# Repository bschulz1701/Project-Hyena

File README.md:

# Project-Hyena
Daughterboard for use with Feather form factor controller, designed to interface with multiple, flexible, low cost sensors at the core of a low cost meteorological sensing system. 

# Repo Outline
#### [Documents](Documents/) 

General document and image storage for repo and README

#### [Hardware](Hardware/)

Current board files (Eagle), Bill of Materials (BoM), and other design documents

#### [Production](Production/)

Contains the various Gerber and pick and place files required to have the Printed Circuit Boards (PCBs) manufactured or populated 

#### [Software](Software/)

The software associated with the piece of hardware, this is usually diagnostic software used for verifying or investigating the hardware

#### [Testing](Testing/)

Scripts and results from the testing process and development process. Contains more detailed information about documented issues among other testing. 

## Overview
* **Type:** Data Logger/Daughterboard 
* **Interfaces:** I<sup>2</sup>C, GPIO, Pulse
* **Release Version:** v0.2 - 2020/07/15

## Features
### On-Board
* Micro SD Card 
* RTC w/Battery Backup
* Temperature/Pressure/RH Sensor
* RGB Ambient Light Sensor
* Reverse Polarity Power Protected Inputs 

### Interface
* Tipping Bucket Input (SPST switch compatible)
* Dedicated Potentiometric Input (x1) 
* Flexible Sensor Inputs (x3)
* Dedicated I<sup>2</sup>C Input (x1) 
* Supports Particle and other Feather based controllers 

## Specifications
* **Sensor Voltage:** 3.3V
* **Sensor Current (Max):** 500mA (Combined)

## Jumper Settings 

**Port Select Jumpers**
| Jumper | Purpose | Position 1 | Position 2 | 
| ------ | ------- | ---------- | ---------- |
| `JP1`	| GPIO vs I<sup>2</sup>C - Port 1 Digital | Select I2C | Select GPIO | 
| `JP2` | GPIO vs I<sup>2</sup>C - Port 1 Analog | Select I2C | Select GPIO | 
| `JP3` | GPIO vs I<sup>2</sup>C - Port 2 Digital | Select I2C | Select GPIO | 
| `JP4` | GPIO vs I<sup>2</sup>C - Port 2 Analog | Select I2C | Select GPIO | 
| `JP5` | GPIO vs I<sup>2</sup>C - Port 3 Digital | Select I2C | Select GPIO | 
| `JP6` | GPIO vs I<sup>2</sup>C - Port 3 Analog | Select I2C | Select GPIO | 
| `JP8` | Power Select (Core vs Ext) - Port 1 | Core Power for Port 1 | External Switched Power for Port 1 |

**Configuration Jumpers**
| Jumper | Purpose | Open | Closed | Default | 
| ------ | ------- | ---------- | ---------- | ----- | 
| `JP7` | Enable Hardware WDT | WDT Disabled | WDT Enabled | Closed |  
| `JP9` | Pullup for Port 1 Digital GPIO | Pullup Disabled | Pullup Enabled | Open |
| `JP10` | Gang On-Board and External I2C Buses | I2C Combined | I2C Isolated | Open | 

## Known Issues/Errata

#### WDT Disable

**Issue:** If using Particle Boron as controller and if you have the WDT disabled (leave `JP7` open), the system fails to run properly, or has sporadic resets. This is likely due to parasitic current on the reset line of the Boron.

**Workaround:** Make sure WDT is enabled by closing `JP7`

#### Solder Jumper Stencil

**Issue:** Depending on the thickness of the solder stencil used for populating the board, the solder jumpers may not bridge when desired. This is due to lack of stencil thickness specification and pad geometry.

**Workaround:** Make a note on the board assembly (if working with a board house) as to which jumpers should be connected (see jumper tables). Otherwise, if assembling manually, check the jumpers are connected, and bridge them using solder wire and a soldering iron if they have failed to jump where desired.

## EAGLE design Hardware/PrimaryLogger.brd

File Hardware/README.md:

# Hardware Overview - Project Hyena

## Files

* [Legacy](Legacy/) - File storage for older hardware versions  
* PrimaryLogger.sch - Eagle Schematic
* PrimaryLogger.brd - Eagle Board File
* [PrimaryLogger_BoM.csv](PrimaryLogger_BoM.csv) - BoM (For reference only, see [Production](../Production) for production ready BoM)
* [PrimaryLogger.pdf](PrimaryLogger_0v2.pdf) - PDF of Schematic 

## I2C Addresses 

| Device | Address | 
| ------ | ------- | 
| MCP23008 | 0x20 | 
| TCS3400 | 0x39 |
| MCP7940 | 0x6F |
| SHTC3 | 0x70 |

## Pinout

| Particle Pin | Hyena Pin Name | Control | Function | 
| ------------ | -------------- | ------- | -------- |
| 8 | `3V3_EXT_EN` | Output | Enables the external 3.3v rail (active high, nominally low) | 
| 7 | `WD_HOLD` | Output | Controls the hardware watchdog timer, pulse high to "feed" timer |
| 6 | `GPIO1D` | IO | General digital IO pin for external sensors (J1 Connector) | 
| 5 | `GPIO2D` | IO | General digital IO pin for external sensors (J2 Connector) | 
| 4 | `GPIO3D` | IO | General digital IO pin for external sensors (J3 Connector) | 
| 3 | `RTC_INT` | Input | Interrupt line from RTC, natively high active low (open drain), triggers on falling edge |
| 2 | `SDA_CTRL` | Output | Used to turn internal I2C on or off (active high, I2C_OB on, natively low) |
| 1 | `SCL` | Output | I2C clock line |
| 0 | `SDA` | IO | I2C Data line |
| 9 | `3V3_SD_EN` | Output | Enable line for SD card 3.3v supply (active high, natively low) |
| 10 | `IO_EXP_INT` | Input | Global interrupt from the IO expander (functionality configurable via software) |
| 11 | `MISO` | Input | MasterInSlaveOut, part of SPI bus |
| 12 | `MOSI` | Output | MasterOutSlaveIn, part of SPI bus | 
| 13 | `SCK` | Output | SerialClocK, part of SPI bus | 
| 14 | `SD_CS` | Output | SD chip select line, active low |
| 15/ADC4 | `TIP` | IO | Designed as tipping bucket rain gauge input, connected to J6, pulled high by default |
| 16/ADC3 | `GPIOXA` | IO | Intended as analog input for potentiometric input (J5) |
| 17/ADC2 | `GPIO1A` | IO | General digital/analog IO pin for external sensors (J1 Connector) |
| 18/ADC1 | `GPIO2A` | IO | General digital/analog IO pin for external sensors (J2 Connector) |
| 19/ADC0 | `GPIO3A` | IO | General digital/analog IO pin for external sensors (J3 Connector) |

| IO Expander Pin | Hyena Pin Name | Control | Function |
| --------------- | -------------- | ------- | -------- |
| 0 | `3V3_EXT_FAULT` | Input | Monitor pin for external 3v3 rail, if over current trip, pin is pulled low, natively high |
| 1 | `3V3_SD_FAULT` | Input | Monitor pin for SD card 3v3 rail, if over current trip, pin is pulled low, natively high |
| 2 | `SD_CD` | Input | Card detect pin for SD card, natively high, pulled low to indicate physical presence of SD card | 
| 3 | `I2C_EXT_EN` | Output | Control line for external I2C buffer, natively high (on), can be pulled low to turn off the external I2C bus | 
| 4 | `PAR_INT` | Input | Event interrupt line from TCS3400 light sensor (used for PAR measurement), active low interrupt |

## Hardware Testing:
See Testing sub folder

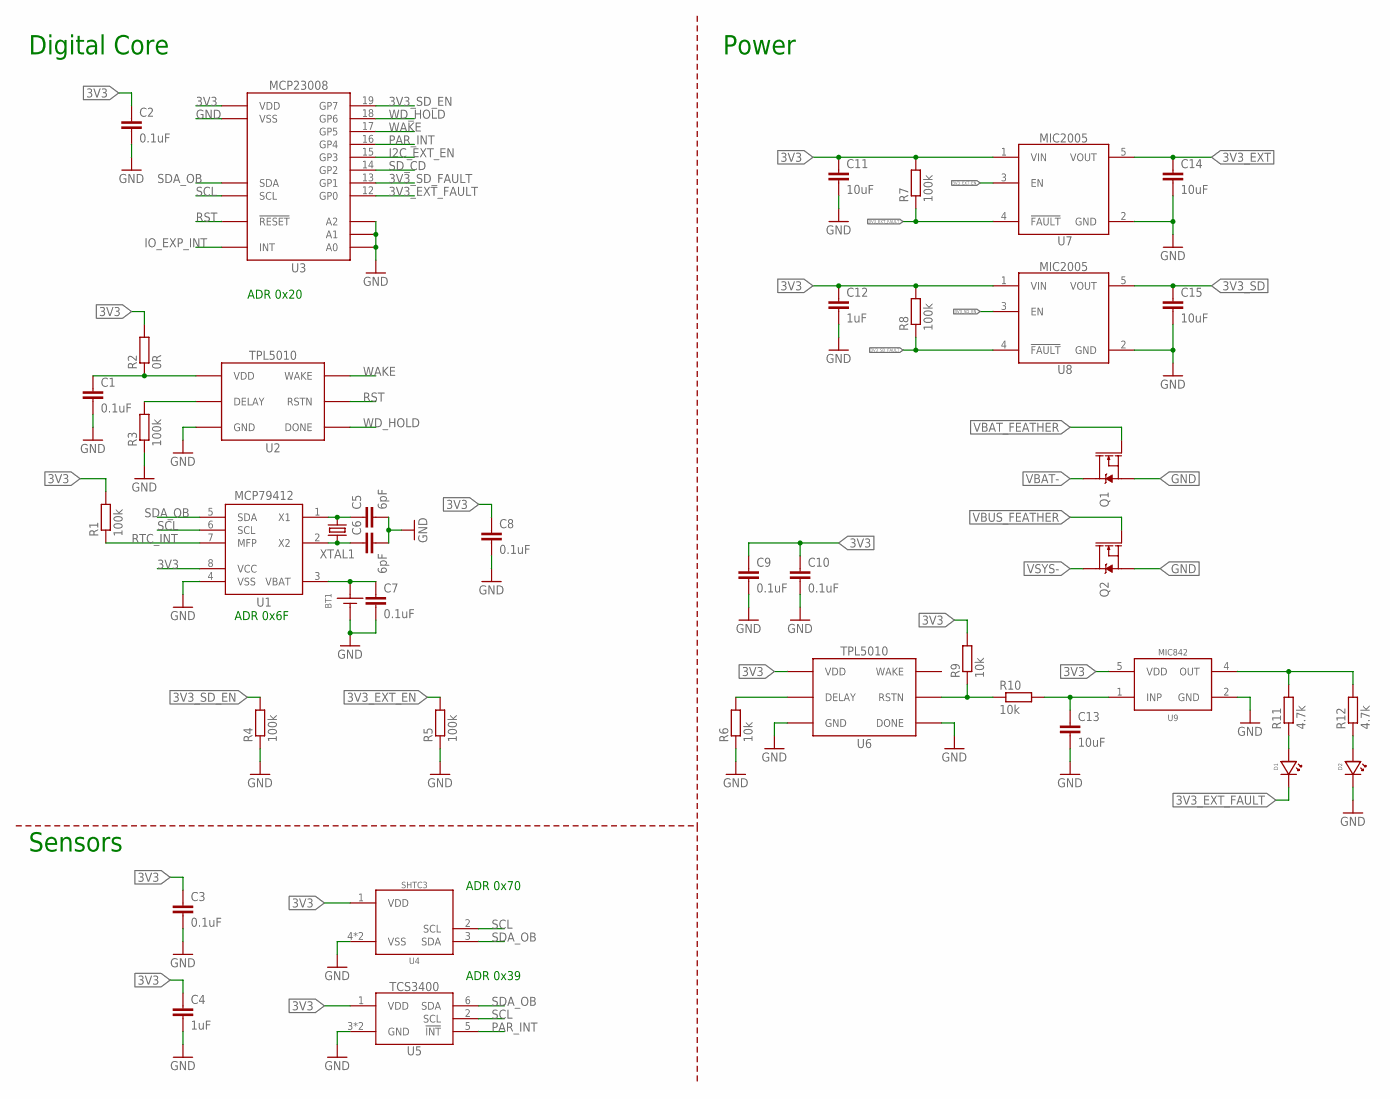
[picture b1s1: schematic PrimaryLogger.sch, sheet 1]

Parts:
BT1: BATTERY_COIN12MM; LINX_BAT-HLD-012-SMT
C1, C2, C3, C7, C8, C9, C10: 0.1uF; C0603
C4, C12: 1uF; C0603
C5, C6: 6pF; C0402
C11, C13, C14, C15: 10uF; C0805
D1: LEDRED0603; LED_0603
D2: LEDGREEN0603; LED_0603
Q1, Q2: DMG3404; SOT23-3
R1, R3, R4, R5, R7, R8: 100k; R0603
R2: 0R; R0603
R6, R9, R10: 10k; R0603
R11, R12: 4.7k; R0603
U1: MCP79412SOIC; SO08
U2, U6: TPL5010DDC; DDC_R-PDSO-G6
U3: MCP23008SSOP; SSOP20
U4: SHTC3DFN; DFN_4_2X2
U5: TCS3400
U7, U8: MIC2005; SOT23-5
U9: MIC842L; DCK_R-PDSO-G5
XTAL1: CRYSTAL3.2X1.5; CRYSTAL_3.2X1.5_2-SMD; MPN Abracon; DIGIKEY 535-11937-1-ND

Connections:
3V3: C2.1, C3.1, C4.1, C8.1, C9.1, C10.1, C11.1, C12.1, R1.2, R2.2, R7.2, R8.2, R9.2, U1.8 (VCC), U3.20 (VDD), U4.1 (VDD), U5.1 (VDD), U6.1 (VDD), U7.1 (VIN), U8.1 (VIN), U9.5 (VDD); also elsewhere on the board
3V3_EXT: C14.1, U7.5 (VOUT); also elsewhere on the board
3V3_EXT_EN: R5.2, U7.3 (EN); also elsewhere on the board
3V3_EXT_FAULT: D1.CATHODE, R7.1, U3.12 (GP0), U7.4 (!FAULT)
3V3_SD: C15.1, U8.5 (VOUT); also elsewhere on the board
3V3_SD_EN: R4.2, U3.19 (GP7), U8.3 (EN)
3V3_SD_FAULT: R8.1, U3.13 (GP1), U8.4 (!FAULT)
GND: BT1.GND (-), C1.2, C2.2, C3.2, C4.2, C5.2, C6.2, C7.2, C8.2, C9.2, C10.2, C11.2, C12.2, C13.2, C14.2, C15.2, D2.CATHODE, Q1.2 (S), Q2.2 (S), R3.1, R4.1, R5.1, R6.1, U1.4 (VSS), U2.2 (GND), U3.3 (A2), U3.4 (A1), U3.5 (A0), U3.9 (VSS), U4.4 (VSS), U4.EP (VSS), U5.3 (GND), U5.4 (GND), U6.2 (GND), U6.4 (DONE), U7.2 (GND), U8.2 (GND), U9.2 (GND); also elsewhere on the board
I2C_EXT_EN: U3.15 (GP3); also elsewhere on the board
IO_EXP_INT: U3.8 (INT); also elsewhere on the board
unnamed: C5.1, U1.1 (X1), XTAL1.P$1 (1)
unnamed: C6.1, U1.2 (X2), XTAL1.P$2 (2)
unnamed: R3.2, U2.3 (DELAY)
unnamed: C1.1, R2.1, U2.1 (VDD)
unnamed: R6.2, U6.3 (DELAY)
unnamed: C13.1, R10.2, U9.1 (INP)
unnamed: R9.1, R10.1, U6.6 (RSTN)
unnamed: R11.2, R12.2, U9.4 (OUT)
unnamed: D1.ANODE, R11.1
unnamed: D2.ANODE, R12.1
PAR_INT: U3.16 (GP4), U5.5 (!INT); also elsewhere on the board
RST: U2.6 (RSTN), U3.6 (!RESET); also elsewhere on the board
RTC_INT: R1.1, U1.7 (MFP); also elsewhere on the board
SCL: U1.6 (SCL), U3.1 (SCL), U4.2 (SCL), U5.2 (SCL); also elsewhere on the board
SDA_OB: U1.5 (SDA), U3.2 (SDA), U4.3 (SDA), U5.6 (SDA); also elsewhere on the board
SD_CD: U3.14 (GP2); also elsewhere on the board
VBAT: BT1.POWER0 (+), BT1.POWER1 (+), C7.1, U1.3 (VBAT)
VBAT-: Q1.3 (D); also elsewhere on the board
VBAT_FEATHER: Q1.1 (G); also elsewhere on the board
VBUS_FEATHER: Q2.1 (G); also elsewhere on the board
VSYS-: Q2.3 (D); also elsewhere on the board
WAKE: U2.5 (WAKE), U3.17 (GP5)
WD_HOLD: U2.4 (DONE), U3.18 (GP6)

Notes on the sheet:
Digital Core
Sensors
Power
ADR 0x39
ADR 0x70
ADR 0x6F
ADR 0x20

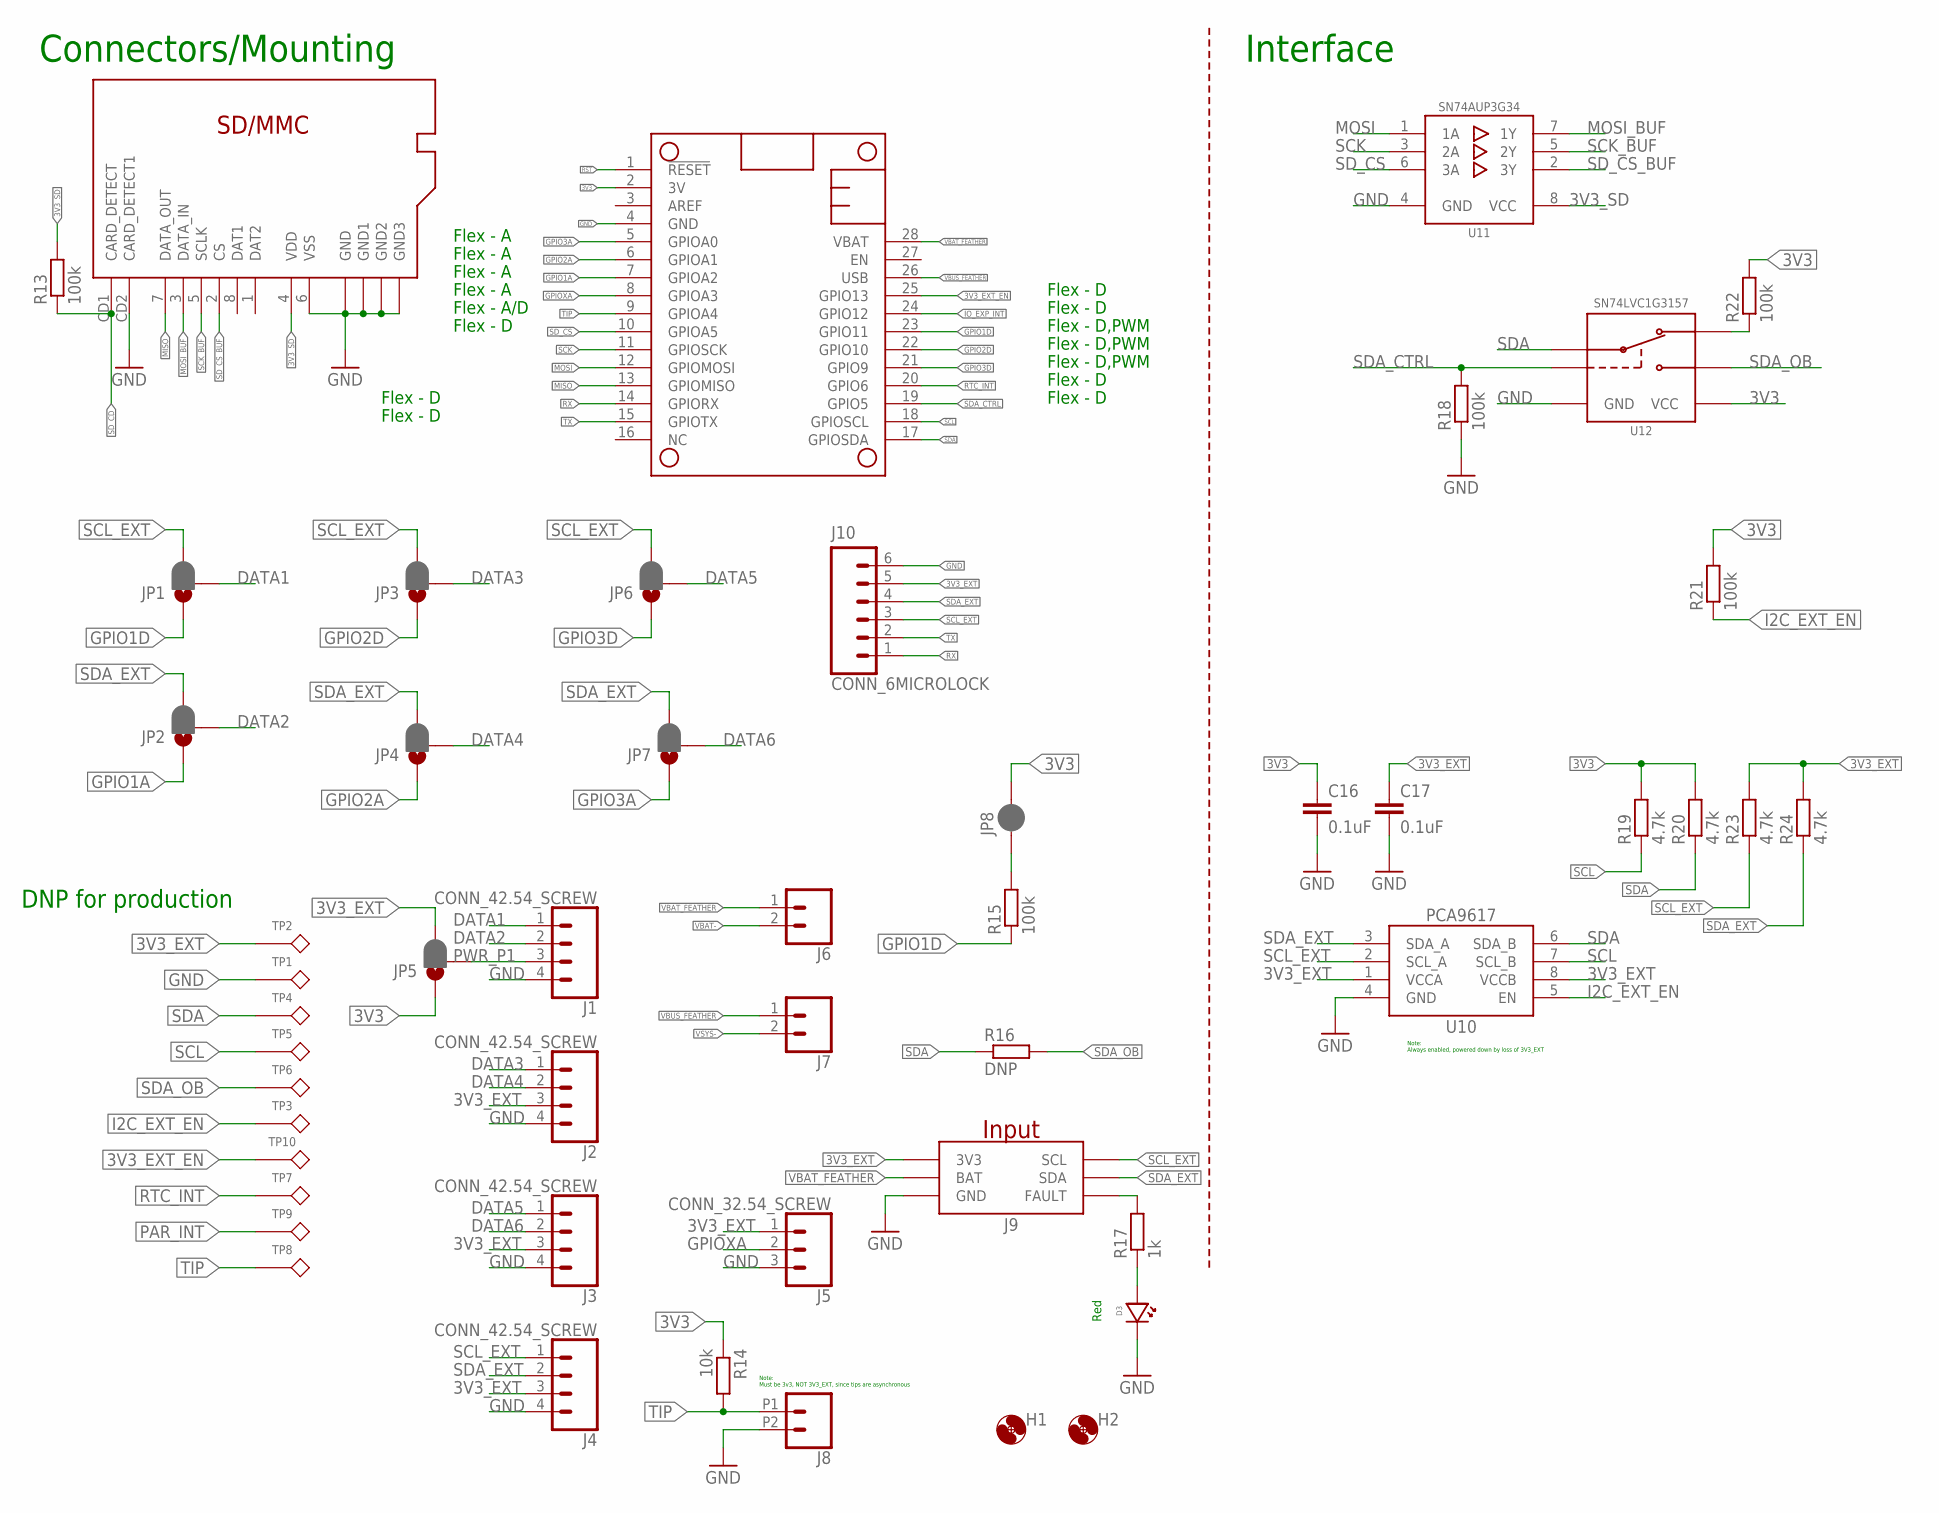
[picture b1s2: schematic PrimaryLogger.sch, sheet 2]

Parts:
C16, C17: 0.1uF; C0603
D3: LEDRED0603; LED_0603
H1, H2: MOUNTING_HOLE2_NP; 2_56
J1, J2, J3, J4: CONN_42.54_SCREW; 1X04_SCREW
J5: CONN_32.54_SCREW; 1X03_SCREW
J6, J7: CONN_023.5MM_ROUND; SCREWTERMINAL-3.5MM-2_ROUND
J8: CONN_022.54_SCREW_ROUND; 1X02_2.54_SCREWTERM_ROUND
J9: GEMS_POWER_PLUGINPUT; 2X3_MICROFIT_RT
J10: CONN_6MICROLOCK; 1X06_MICROLOCKPLUS
JP1, JP2, JP3, JP4, JP5, JP6, JP7: JUMPER-SMT_3_1-NC_PASTE_SILK; SMT-JUMPER_3_1-NC_PASTE_SILK
JP8: JUMPER-SMT_2_NC_PASTE_SILK; SMT-JUMPER_2_NC_PASTE_SILK
MS1: FEATHERWINGLAYOUT; FEATHERWING_MIN
R13, R15, R18, R21, R22: 100k; R0603
R14: 10k; R0603
R16: DNP; R0603
R17: 1k; R0603
R19, R20, R23, R24: 4.7k; R0603
SD1: MICRO_SD; CUSTOM-PARTS_SD_MICRO
TP1, TP2, TP3, TP4, TP5, TP6, TP7, TP8, TP9, TP10: TESTPOINTRCU; TESTPOINT_0603
U10: PCA9617; TSSOP_8
U11: SN74AUP3G34DCU; DCU_(R-PDSO-G8)
U12: SN74LVC1G3157SC70; DCK_R-PDSO-G6

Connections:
3V3: C16.1, JP5.1, JP8.2, MS1.2 (3V), R14.1, R19.2, R20.2, R21.2, R22.2, U12.5 (VCC); also elsewhere on the board
3V3_EXT: C17.1, J2.3, J3.3, J4.3, J5.1, J9.5 (3V3), J10.5, JP5.3, R23.2, R24.2, TP2.1, U10.1 (VCCA), U10.8 (VCCB); also elsewhere on the board
3V3_EXT_EN: MS1.25 (GPIO13), TP10.1; also elsewhere on the board
3V3_SD: R13.2, SD1.4 (VDD), U11.8 (VCC); also elsewhere on the board
DATA1: J1.1, JP1.2
DATA2: J1.2, JP2.2
DATA3: J2.1, JP3.2
DATA4: J2.2, JP4.2
DATA5: J3.1, JP6.2
DATA6: J3.2, JP7.2
GND: C16.2, C17.2, D3.CATHODE, J1.4, J2.4, J3.4, J4.4, J5.3, J8.P2 (2), J9.2 (GND), J10.6, MS1.4 (GND), R18.1, SD1.6 (VSS), SD1.CD2 (CARD_DETECT1), SD1.GND@1 (GND), SD1.GND@2 (GND1), SD1.GND@3 (GND2), SD1.GND@5 (GND3), TP1.1, U10.4 (GND), U11.4 (GND), U12.2 (GND); also elsewhere on the board
GPIO1A: JP2.1, MS1.7 (GPIOA2)
GPIO1D: JP1.1, MS1.23 (GPIO11), R15.1
GPIO2A: JP4.1, MS1.6 (GPIOA1)
GPIO2D: JP3.1, MS1.22 (GPIO10)
GPIO3A: JP7.1, MS1.5 (GPIOA0)
GPIO3D: JP6.1, MS1.21 (GPIO9)
GPIOXA: J5.2, MS1.8 (GPIOA3)
I2C_EXT_EN: R21.1, TP3.1, U10.5 (EN); also elsewhere on the board
IO_EXP_INT: MS1.24 (GPIO12); also elsewhere on the board
MISO: MS1.13 (GPIOMISO), SD1.7 (DATA_OUT)
MOSI: MS1.12 (GPIOMOSI), U11.1 (1A)
MOSI_BUF: SD1.3 (DATA_IN), U11.7 (1Y)
unnamed: R22.1, U12.3 (B1)
unnamed: JP8.1, R15.2
unnamed: J9.3 (FAULT), R17.2
unnamed: D3.ANODE, R17.1
PAR_INT: TP9.1; also elsewhere on the board
PWR_P1: J1.3, JP5.2
RST: MS1.1 (!RESET); also elsewhere on the board
RTC_INT: MS1.20 (GPIO6), TP7.1; also elsewhere on the board
RX: J10.1, MS1.14 (GPIORX)
SCK: MS1.11 (GPIOSCK), U11.3 (2A)
SCK_BUF: SD1.5 (SCLK), U11.5 (2Y)
SCL: MS1.18 (GPIOSCL), R19.1, TP5.1, U10.7 (SCL_B); also elsewhere on the board
SCL_EXT: J4.1, J9.6 (SCL), J10.3, JP1.3, JP3.3, JP6.3, R23.1, U10.2 (SCL_A)
SDA: MS1.17 (GPIOSDA), R16.1, R20.1, TP4.1, U10.6 (SDA_B), U12.4 (A)
SDA_CTRL: MS1.19 (GPIO5), R18.2, U12.6 (S)
SDA_EXT: J4.2, J9.4 (SDA), J10.4, JP2.3, JP4.3, JP7.3, R24.1, U10.3 (SDA_A)
SDA_OB: R16.2, TP6.1, U12.1 (B2); also elsewhere on the board
SD_CD: R13.1, SD1.CD1 (CARD_DETECT); also elsewhere on the board
SD_CS: MS1.10 (GPIOA5), U11.6 (3A)
SD_CS_BUF: SD1.2 (CS), U11.2 (3Y)
TIP: J8.P1 (1), MS1.9 (GPIOA4), R14.2, TP8.1
TX: J10.2, MS1.15 (GPIOTX)
VBAT-: J6.2; also elsewhere on the board
VBAT_FEATHER: J6.1, J9.1 (BAT), MS1.28 (VBAT); also elsewhere on the board
VBUS_FEATHER: J7.1, MS1.26 (USB); also elsewhere on the board
VSYS-: J7.2; also elsewhere on the board

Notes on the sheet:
Note: Must be 3v3, NOT 3V3_EXT, since tips are asynchronous
DNP for production
Flex - A
Flex - A/D
Flex - D
Flex - D,PWM
Note: Always enabled, powered down by loss of 3V3_EXT
Connectors/Mounting
Interface
Red

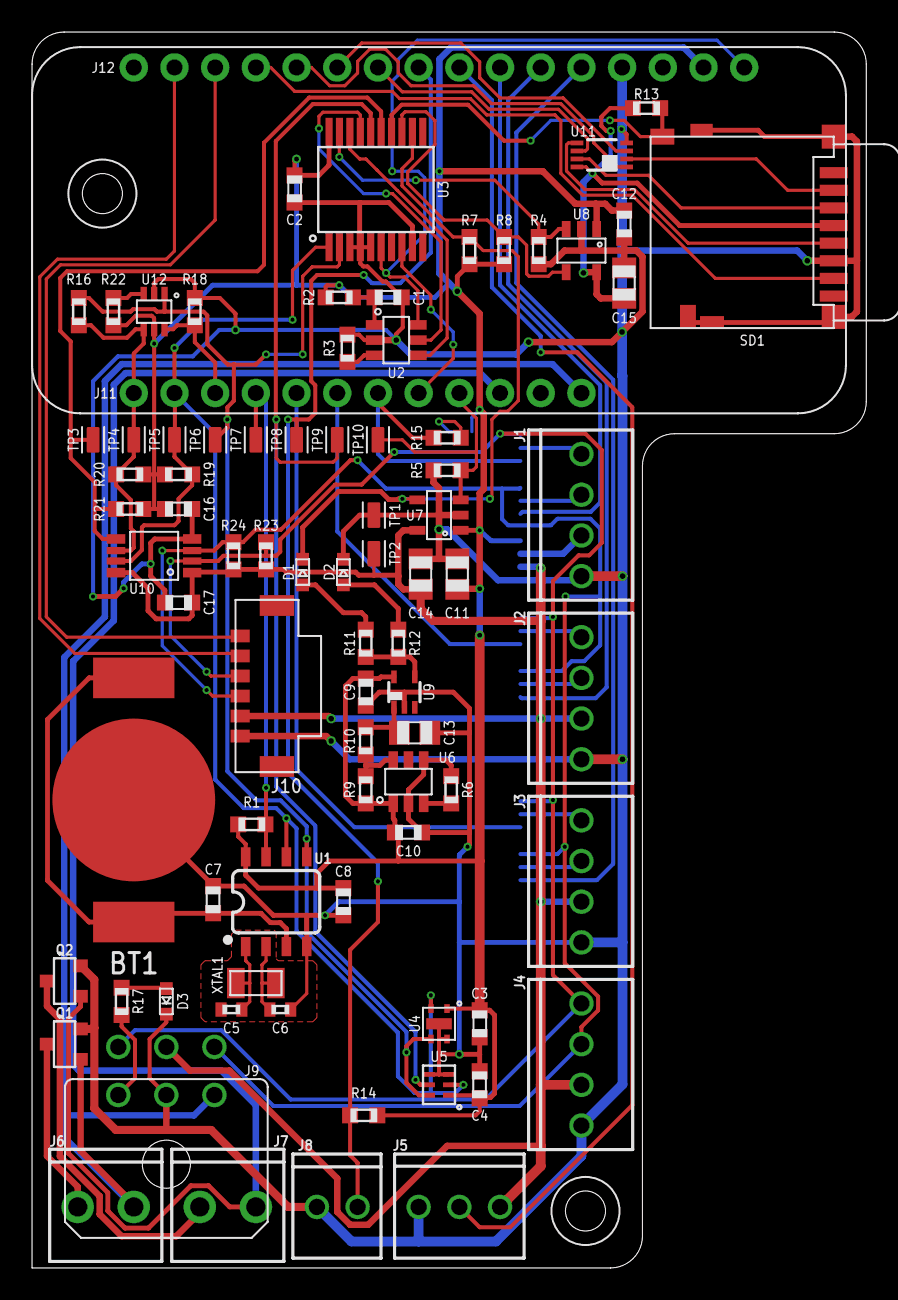
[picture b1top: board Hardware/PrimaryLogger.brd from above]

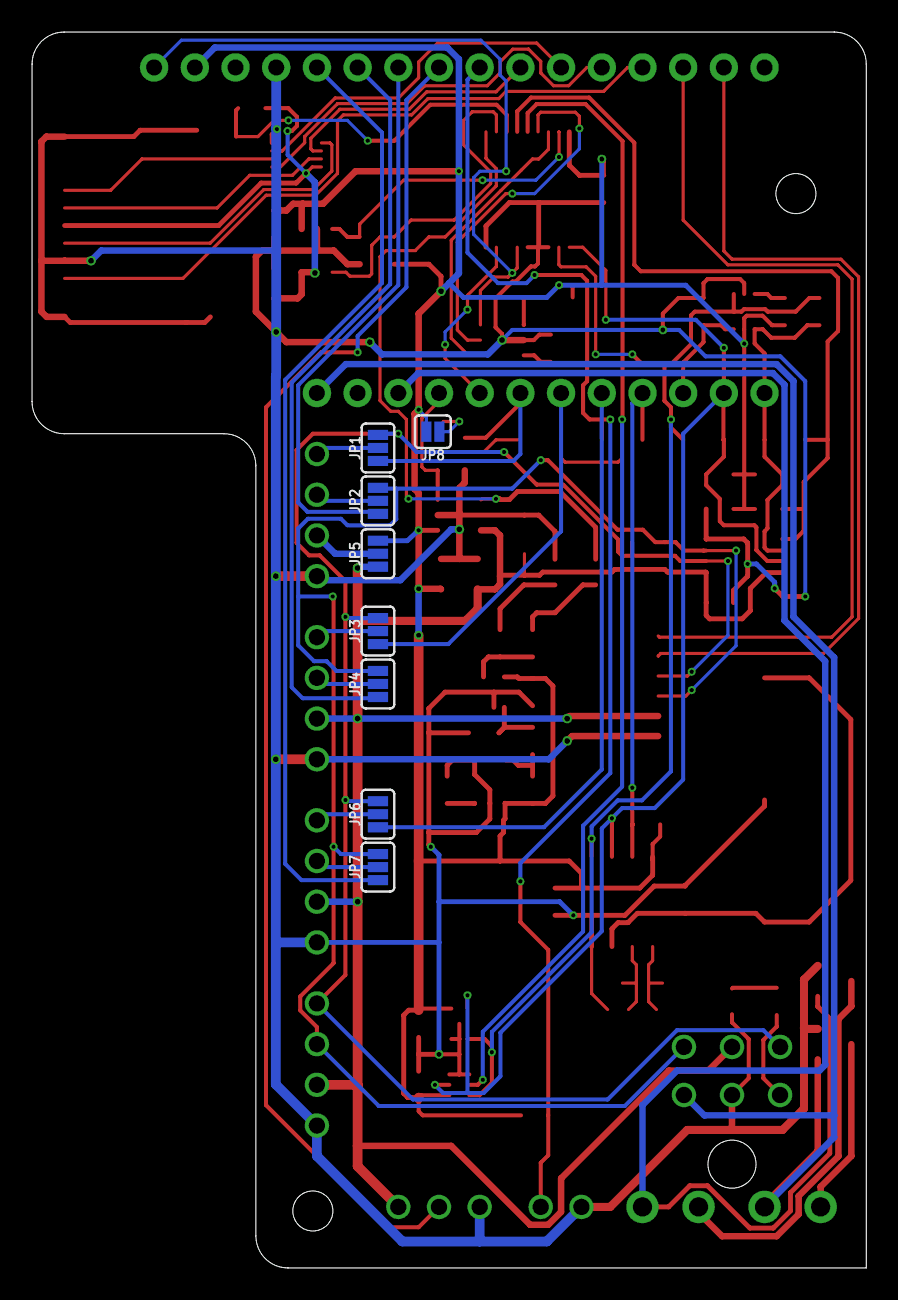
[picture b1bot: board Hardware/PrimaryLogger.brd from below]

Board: 2 copper layers, 52.1 x 77.1 mm, 92 parts (8 on the bottom side), 65 nets.

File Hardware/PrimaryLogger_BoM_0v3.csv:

"Qty","Value","Device","Package","Parts","Description","DIGIKEY","DISP","MF","MPN","VALUE","VALUE_PART",
"1","","CONN_022.54_SCREW_ROUND","1X02_2.54_SCREWTERM_ROUND","J8","Genaric 2 terminal header","ED10561-ND","","OnShore","OSTVN02A150","","",
"2","","CONN_023.5MM_ROUND","SCREWTERMINAL-3.5MM-2_ROUND","J6, J7","Genaric 2 terminal header","ED2635-ND","","OnShore","OSTTE020161","","",
"2","","MOUNTING_HOLE2_NP","2_56","H1, H2","Genaric Mechanical Mounting Hole","DNP","","N/A","DNP","","",
"9","0.1uF","C-EU0.1UFC0603","C0603","C1, C2, C3, C7, C8, C9, C10, C16, C17","CAPACITOR, European symbol","490-6051-1-ND","","Murata","GCM188R71E104KA57D","","",
"2","0R","R-EU_0.0R0603","R0603","R2, R16","RESISTOR, European symbol","311-0.0LECT-ND","","Yageo","AC0603JR-070RL","","0",
"11","100k","R-EU_100KR0603","R0603","R1, R3, R4, R5, R7, R8, R13, R15, R18, R21, R22","RESISTOR, European symbol","311-100KHRCT-ND","","Yageo","RC0603FR-07100KL","","100k",
"4","10k","R-EU_10KR0603","R0603","R6, R9, R10, R14","RESISTOR, European symbol","311-10.0KHRCT-ND","","Yageo","RC0603FR-0710KL","","10k",
"4","10uF","C-EU10UFC0805","C0805","C11, C13, C14, C15","CAPACITOR, European symbol","490-6473-6-ND","","Murata","GRM21BR61C106KE15K","","",
"1","1k","R-EU_1KR0603","R0603","R17","RESISTOR, European symbol","311-1KLDCT-ND","","Yageo","AC0603FR-071KL","","1k",
"2","1uF","C-EU1UFC0603","C0603","C4, C12","CAPACITOR, European symbol","587-1251-1-ND","","Yaiyo Yuden","EMK107BJ105KA-T","","",
"6","4.7k","R-EU_4.7KR0603","R0603","R11, R12, R19, R20, R23, R24","RESISTOR, European symbol","311-4.70KHRCT-ND","","Yageo","RC0603FR-074K7L","","4.7k",
"2","6pF","C-EU6PFC0402","C0402","C5, C6","CAPACITOR, European symbol","490-3104-1-ND","","Murata","GJM1555C1H6R0CB01D","","",
"1","BATTERY_COIN12MM","BATTERY_COIN12MM","LINX_BAT-HLD-012-SMT","BT1","Coin Cell Battery Holder","BAT-HLD-012-SMT-ND","","Linx","BAT-HLD-012-SMT","","",
"1","CONN_32.54_SCREW","CONN_32.54_SCREW","1X03_SCREW","J5","Genaric 3 terminal header","ED10562-ND","","On Shore","OSTVN03A150","","",
"4","CONN_42.54_SCREW","CONN_42.54_SCREW","1X04_SCREW","J1, J2, J3, J4","Genaric 4 terminal header","ED10563-ND","","On Shore","OSTVN04A150","","",
"1","CRYSTAL3.2X1.5","CRYSTAL3.2X1.5","CRYSTAL_3.2X1.5_2-SMD","XTAL1","Crystal Oscilator","535-11937-1-ND","","ABS07-120-32.768KHZ-T","Abracon","","",
"2","DMG3404","MOSFET-NCH-DMG3404L","SOT23-3","Q1, Q2","N-channel MOSFETs","DMG3404L-7DICT-ND","","Diodes Incorporated","DMG3404L-7","DMG3404","",
"1","FEATHERWING_NODIM","FEATHERWING_NODIM","FEATHERWING_DIM","MS1","","","","","","","",
"1","GEMS_POWER_PLUGINPUT","GEMS_POWER_PLUGINPUT","2X3_MICROFIT_RT","J9","Power Plug For GEMS Based SystemsBoth Input and Output versions","WM1815-ND","Input","Molex","0430450600","","",
"1","JUMPER-SMT_2_NC_PASTE_SILK","JUMPER-SMT_2_NC_PASTE_SILK","SMT-JUMPER_2_NC_PASTE_SILK","JP8","Normally closed solder jumper","DNP","","N/A","N/A","","",
"7","JUMPER-SMT_3_1-NC_PASTE_SILK","JUMPER-SMT_3_1-NC_PASTE_SILK","SMT-JUMPER_3_1-NC_PASTE_SILK","JP1, JP2, JP3, JP4, JP5, JP6, JP7","Normally closed solder jumper (1 of 2 connections)","DNP","","N/A","N/A","","",
"1","LEDGREEN0603","LEDGREEN0603","LED_0603","D2","Genaric LED","732-4971-1-ND","","Wurth","150060GS75000","","",
"2","LEDRED0603","LEDRED0603","LED_0603","D1, D3","Genaric LED","732-4978-1-ND","","Wurth","150060RS75000","","",
"1","MCP23008SSOP","MCP23008SSOP","SSOP20","U3","MCP23008 - I2C I/O Expander, 8 bit wtih interrupt and reset","MCP23008T-E/SSCT-ND","","Microchip","MCP23008T-E/SS","","",
"1","MCP79412SOIC","MCP79412SOIC","SO08","U1","MCP794xx - Battery Backed I2C Real Time Clock (RTC) with SRAM (EEPROM*) and Protected EERPOM","MCP79412-I/SN-ND","MCP79412","Microchip","MCP79412-I/SN","","",
"2","MIC2005","MIC2005","SOT23-5","U7, U8","MIC2005 - Hight Side Load Switch, with Fixed Current Limit","576-3462-1-ND","MIC2005","Microchip","MIC2005A-1YM5-TR","","",
"1","MIC842L","MIC842L","DCK_R-PDSO-G5","U9","Comparator with internal voltage referance (1.24V), 5V and 3.3V compatable, 20mA output current","576-2927-1-ND","","Microchip","MIC842LYC5-TR","","",
"1","MICRO_SD","MICRO_SD","CUSTOM-PARTS_SD_MICRO","SD1","Micro SD Card - Card Detect, Exposed leads for non-reflow soldering","114-00841-68-1-ND","","Amphenol","114-00841-68","","",
"1","PCA9617TSSOP8","PCA9617TSSOP8","TTSOP_8","U10","PCA9617A - Level translating I2C Bus Repeater","568-10211-2-ND","","NXP","PCA9617ADPJ","","",
"1","SHTC3DFN","SHTC3DFN","DFN_4_2X2","U4","SHTCx - Digital Humidity and Temperature Sensor","1649-1100-1-ND","SHTC3","Sensirion","SHTC3","","",
"1","SN74AUP3G34DCU","SN74AUP3G34DCU","DCU_(R-PDSO-G8)","U11","SN74AUP3G34 - Logic Buffer","296-25595-1-ND","","TI","SN74AUP3G34DCUR","","",
"1","SN74LVC1G3157SC70","SN74LVC1G3157SC70","DCK_R-PDSO-G6","U12","SN74LVC1G3157 - SPDT Analog Switch","296-14909-1-ND","SN74LVC1G3157","TI","SN74LVC1G3157DCKR","","",
"1","TCS3400","TCS3400","TCS3400","U5","TCS3400 - Ambient Multi-Band Light Sensor with I2C Interface","TCS34003FNMCT-ND","","AMS","TCS34003FNM","","",
"10","TESTPOINTRCU","TESTPOINTRCU","TESTPOINT_0603","TP1, TP2, TP3, TP4, TP5, TP6, TP7, TP8, TP9, TP10","","A106145CT-ND","","TE Connectivity","RCU-0C","","",
"2","TPL5010DDC","TPL5010DDC","DDC_R-PDSO-G6","U2, U6","TPL5010 - Nano-Power System Timer with Watchdog Functionality","296-38829-1-ND","","TI","TPL5010DDCT","","",

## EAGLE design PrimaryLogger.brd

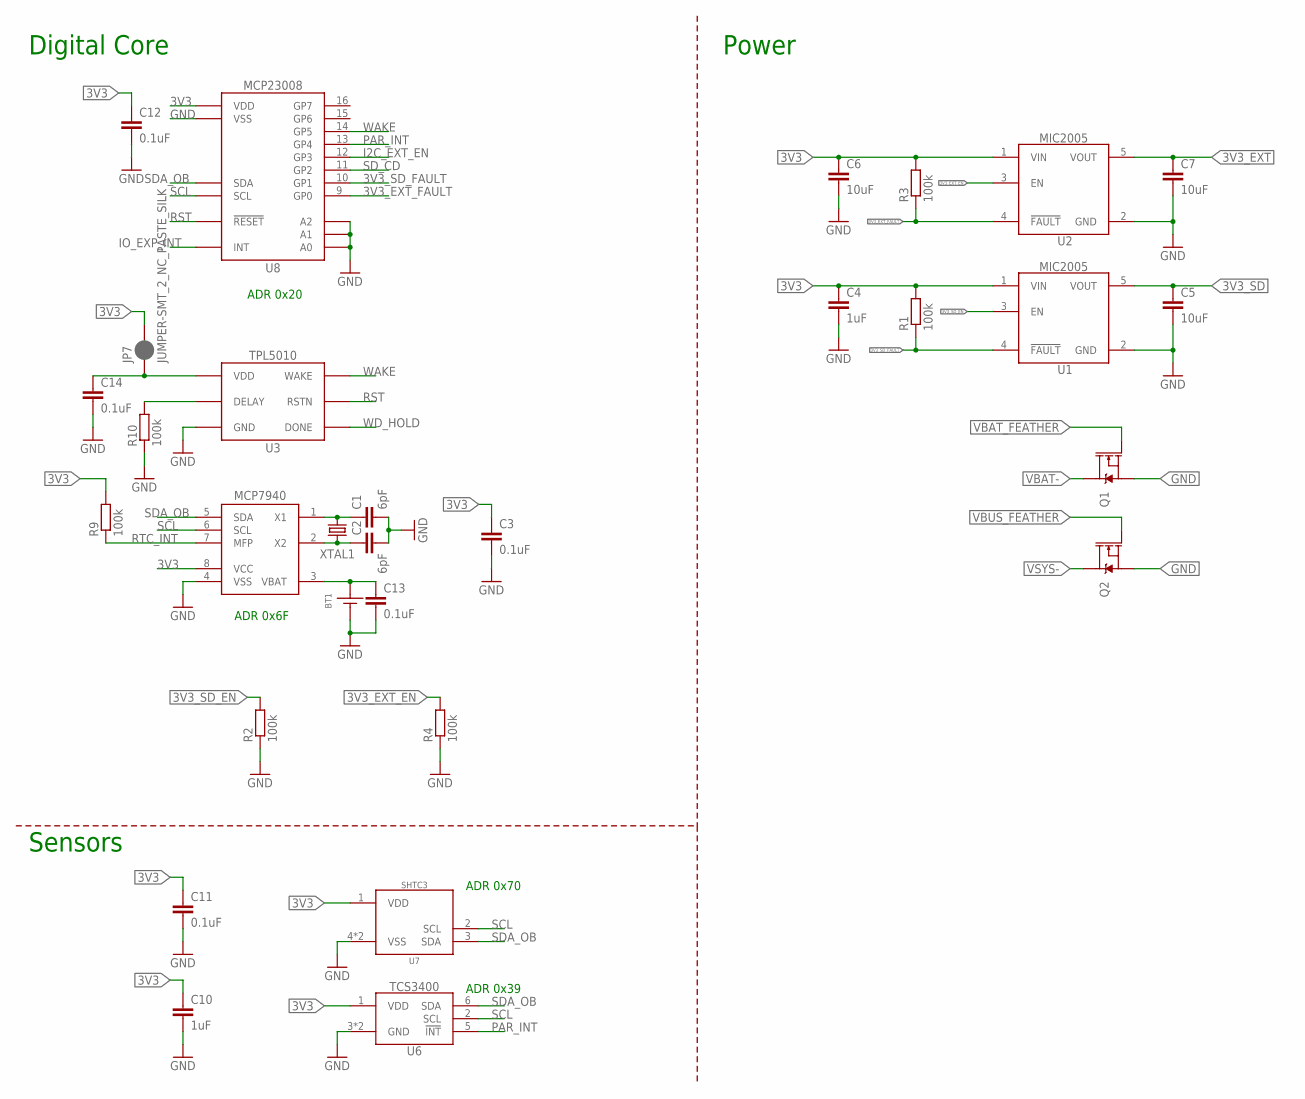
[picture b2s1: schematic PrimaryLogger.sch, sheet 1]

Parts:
BT1: BATTERY_COIN12MM; LINX_BAT-HLD-012-SMT
C1, C2: 6pF; C0402
C3, C11, C12, C13, C14: 0.1uF; C0603
C4, C10: 1uF; C0603
C5, C6, C7: 10uF; C0805
JP7: JUMPER-SMT_2_NC_PASTE_SILK; SMT-JUMPER_2_NC_PASTE_SILK
Q1, Q2: DMG3404; SOT23-3
R1, R2, R3, R4, R9, R10: 100k; R0603
U1, U2: MIC2005; SOT23-5
U3: TPL5010DDC; DDC_R-PDSO-G6
U6: TCS3400
U7: SHTC3DFN; DFN_4_2X2
U8: MCP23008QFN; QFN20
U9: MCP7940SOIC; SO08
XTAL1: CRYSTAL3.2X1.5; CRYSTAL_3.2X1.5_2-SMD; MPN Abracon; DIGIKEY 535-11937-1-ND

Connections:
3V3: C3.1, C4.1, C6.1, C10.1, C11.1, C12.1, JP7.2, R1.2, R3.2, R9.2, U1.1 (VIN), U2.1 (VIN), U6.1 (VDD), U7.1 (VDD), U8.18 (VDD), U9.8 (VCC); also elsewhere on the board
3V3_EXT: C7.1, U2.5 (VOUT); also elsewhere on the board
3V3_EXT_EN: R4.2, U2.3 (EN); also elsewhere on the board
3V3_EXT_FAULT: R3.1, U2.4 (!FAULT), U8.9 (GP0)
3V3_SD: C5.1, U1.5 (VOUT); also elsewhere on the board
3V3_SD_EN: R2.2, U1.3 (EN); also elsewhere on the board
3V3_SD_FAULT: R1.1, U1.4 (!FAULT), U8.10 (GP1)
GND: BT1.GND (-), C1.2, C2.2, C3.2, C4.2, C5.2, C6.2, C7.2, C10.2, C11.2, C12.2, C13.2, C14.2, Q1.2 (S), Q2.2 (S), R2.1, R4.1, R10.1, U1.2 (GND), U2.2 (GND), U3.2 (GND), U6.3 (GND), U6.4 (GND), U7.4 (VSS), U7.EP (VSS), U8.1 (A2), U8.2 (A1), U8.3 (A0), U8.17 (VSS), U8.EP (VSS), U9.4 (VSS); also elsewhere on the board
I2C_EXT_EN: U8.12 (GP3); also elsewhere on the board
IO_EXP_INT: U8.7 (INT); also elsewhere on the board
unnamed: C1.1, U9.1 (X1), XTAL1.P$1 (1)
unnamed: C2.1, U9.2 (X2), XTAL1.P$2 (2)
unnamed: R10.2, U3.3 (DELAY)
unnamed: C14.1, JP7.1, U3.1 (VDD)
PAR_INT: U6.5 (!INT), U8.13 (GP4); also elsewhere on the board
RST: U3.6 (RSTN), U8.4 (!RESET); also elsewhere on the board
RTC_INT: R9.1, U9.7 (MFP); also elsewhere on the board
SCL: U6.2 (SCL), U7.2 (SCL), U8.19 (SCL), U9.6 (SCL); also elsewhere on the board
SDA_OB: U6.6 (SDA), U7.3 (SDA), U8.20 (SDA), U9.5 (SDA); also elsewhere on the board
SD_CD: U8.11 (GP2); also elsewhere on the board
VBAT: BT1.POWER0 (+), BT1.POWER1 (+), C13.1, U9.3 (VBAT)
VBAT-: Q1.3 (D); also elsewhere on the board
VBAT_FEATHER: Q1.1 (G); also elsewhere on the board
VBUS_FEATHER: Q2.1 (G); also elsewhere on the board
VSYS-: Q2.3 (D); also elsewhere on the board
WAKE: U3.5 (WAKE), U8.14 (GP5)
WD_HOLD: U3.4 (DONE); also elsewhere on the board

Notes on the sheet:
Digital Core
Sensors
Power
ADR 0x39
ADR 0x70
ADR 0x6F
ADR 0x20

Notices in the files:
parts and their libraries:
bschulz: This work is licensed under the Creative Commons Attribution-ShareAlike 4.0
http://creativecommons.org/licenses/by-sa/4.0
